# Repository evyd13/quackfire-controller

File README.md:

# Quackfire controller rev1

This is a replacement controller for the CM Quickfire Rapid. Everything works, except for the WinLock LED (which isn't connected to the controller).

## Building
If you feel like building a few of these PCBs yourself, go to the 'Releases' tab and download the latest gerber files. Order those at your favourite PCB manufacturer, get the components needed (see below) and solder them on! A hot air station is not required but a good soldering iron is. Flux is recommended.

## Opening the project
To open the files you will need the latest KiCAD nightly version.

## Bill of materials (BOM)
Amount is per PCB, multiply as needed.

| LCSC part # | Description             | Value | Package  | Amount |
| ----------- | ----------------------- | ----- | -------- | ------:|
| C83060      | Capacitor               | 0.1uF | 0603     | 4      |
| C131056     | Capacitor               | 4.7uF | 0805     | 1      |
| C302042     | Capacitor               | 1uF   | 0603     | 1      |
| C261942     | Fuse                    |       | 0805     | 1      |
| C98220      | Resistor                | 10K   | 0603     | 2      |
| C12028      | Resistor                | 5.1K  | 0603     | 2      |
| C384264     | Resistor                | 22    | 0603     | 2      |
| C44854      | MCU                     | 32U4  | QFP-44   | 1      |
| C341521     | Resonator               | 16MHz | SMD      | 1      |
|             | 2x10 2.00mm pin header  |       | THT      | 2      |

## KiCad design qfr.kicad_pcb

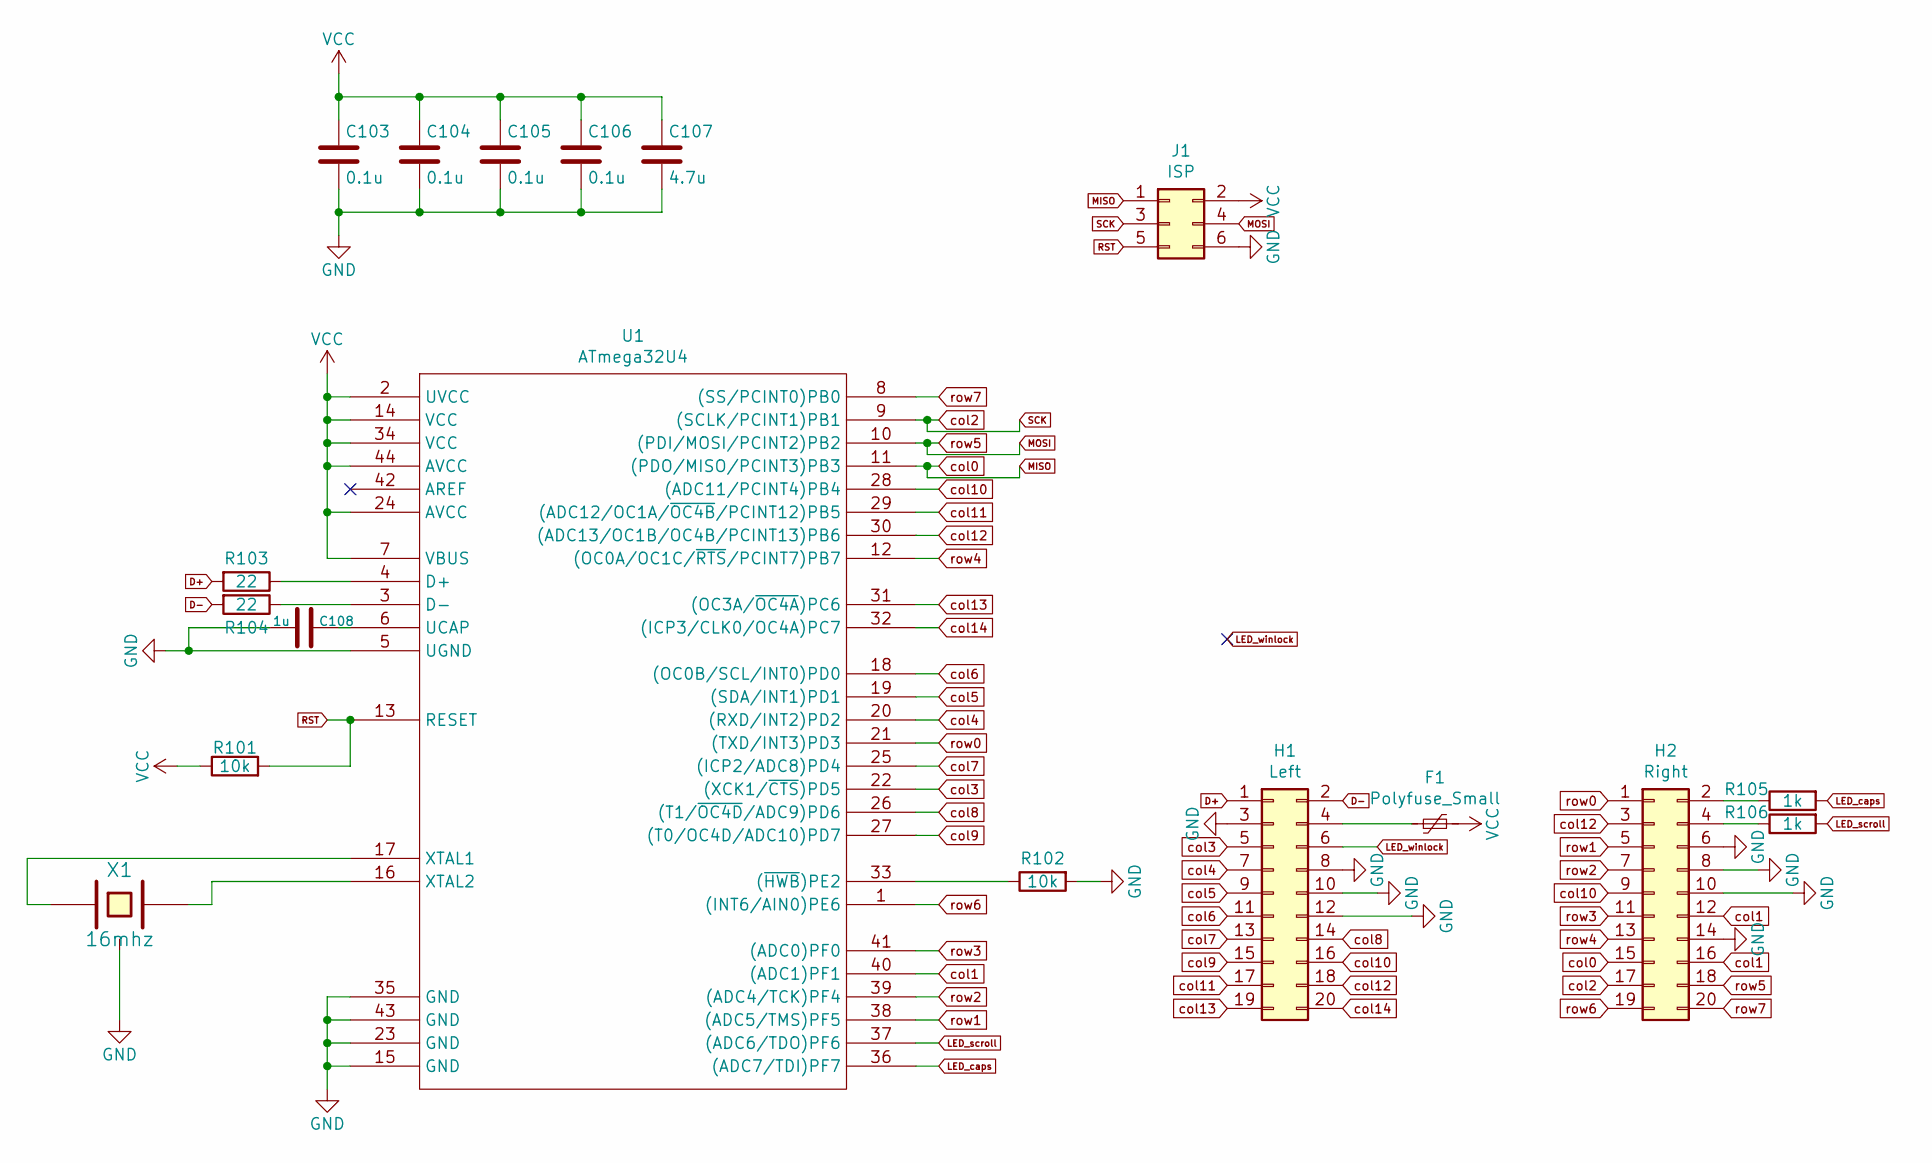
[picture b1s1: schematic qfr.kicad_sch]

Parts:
C103, C104, C105, C106: 0.1u; C_0603
C107: 4.7u; C_0805
C108: 1u; C_0603
F1: Polyfuse_Small; R_0805
H1: Left; PinHeader_2x10_P2.00mm_Vertical
H2: Right; PinHeader_2x10_P2.00mm_Vertical
J1: ISP; isp_standard
R101, R102: 10k; R_0603
R103, R104: 22; R_0603
R105, R106: 1k; R_0603
U1: ATmega32U4; ATMEGA32U4
X1: 16mhz; Resonator_SMD_muRata_CSTNExxV-3Pin-p1.2

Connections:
D+: H1.1, R103.2
D-: H1.2, R104.2
GND: C103.2, C104.2, C105.2, C106.2, C107.2, C108.2, H1.3, H1.8, H1.10, H1.12, H2.6, H2.8, H2.10, H2.14, J1.6, R102.2, U1.5 (UGND), U1.15 (GND), U1.23 (GND), U1.35 (GND), U1.43 (GND), X1.3
LED_caps: R105.2, U1.36 ((ADC7/TDI)PF7)
LED_scroll: R106.2, U1.37 ((ADC6/TDO)PF6)
MISO: H2.15, J1.1, U1.11 ((PDO/MISO/PCINT3)PB3)
MOSI: H2.18, J1.4, U1.10 ((PDI/MOSI/PCINT2)PB2)
unnamed: C108.1, U1.6 (UCAP)
unnamed: F1.1, H1.4
unnamed: H2.2, R105.1
unnamed: H2.4, R106.1
unnamed: R102.1, U1.33 ((~HWB~)PE2)
unnamed: R103.1, U1.4 (D+)
unnamed: R104.1, U1.3 (D-)
unnamed: U1.16 (XTAL2), X1.2
unnamed: U1.17 (XTAL1), X1.1
RST: J1.5, R101.2, U1.13 (RESET)
SCK: H2.17, J1.3, U1.9 ((SCLK/PCINT1)PB1)
VCC: C103.1, C104.1, C105.1, C106.1, C107.1, F1.2, J1.2, R101.1, U1.2 (UVCC), U1.7 (VBUS), U1.14 (VCC), U1.24 (AVCC), U1.34 (VCC), U1.44 (AVCC)
col1: H2.12, H2.16, U1.40 ((ADC1)PF1)
col3: H1.5, U1.22 ((XCK1/~CTS~)PD5)
col4: H1.7, U1.20 ((RXD/INT2)PD2)
col5: H1.9, U1.19 ((SDA/INT1)PD1)
col6: H1.11, U1.18 ((OC0B/SCL/INT0)PD0)
col7: H1.13, U1.25 ((ICP2/ADC8)PD4)
col8: H1.14, U1.26 ((T1/~OC4D~/ADC9)PD6)
col9: H1.15, U1.27 ((T0/OC4D/ADC10)PD7)
col10: H1.16, H2.9, U1.28 ((ADC11/PCINT4)PB4)
col11: H1.17, U1.29 ((ADC12/OC1A/~OC4B~/PCINT12)PB5)
col12: H1.18, H2.3, U1.30 ((ADC13/OC1B/OC4B/PCINT13)PB6)
col13: H1.19, U1.31 ((OC3A/~OC4A~)PC6)
col14: H1.20, U1.32 ((ICP3/CLK0/OC4A)PC7)
row0: H2.1, U1.21 ((TXD/INT3)PD3)
row1: H2.5, U1.38 ((ADC5/TMS)PF5)
row2: H2.7, U1.39 ((ADC4/TCK)PF4)
row3: H2.11, U1.41 ((ADC0)PF0)
row4: H2.13, U1.12 ((OC0A/OC1C/~RTS~/PCINT7)PB7)
row6: H2.19, U1.1 ((INT6/AIN0)PE6)
row7: H2.20, U1.8 ((SS/PCINT0)PB0)

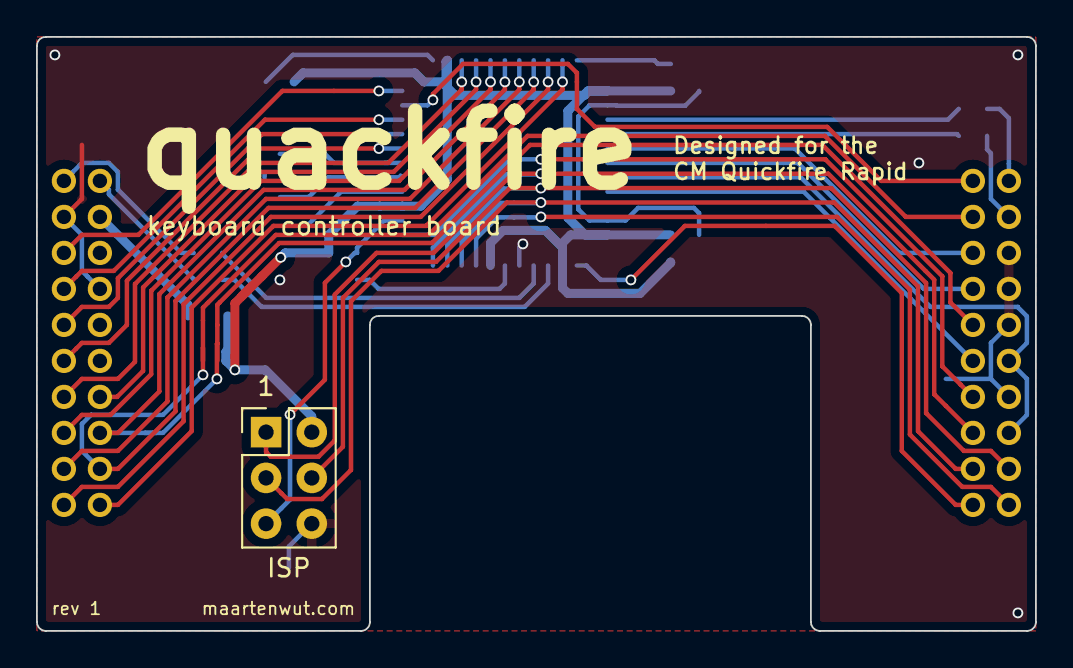
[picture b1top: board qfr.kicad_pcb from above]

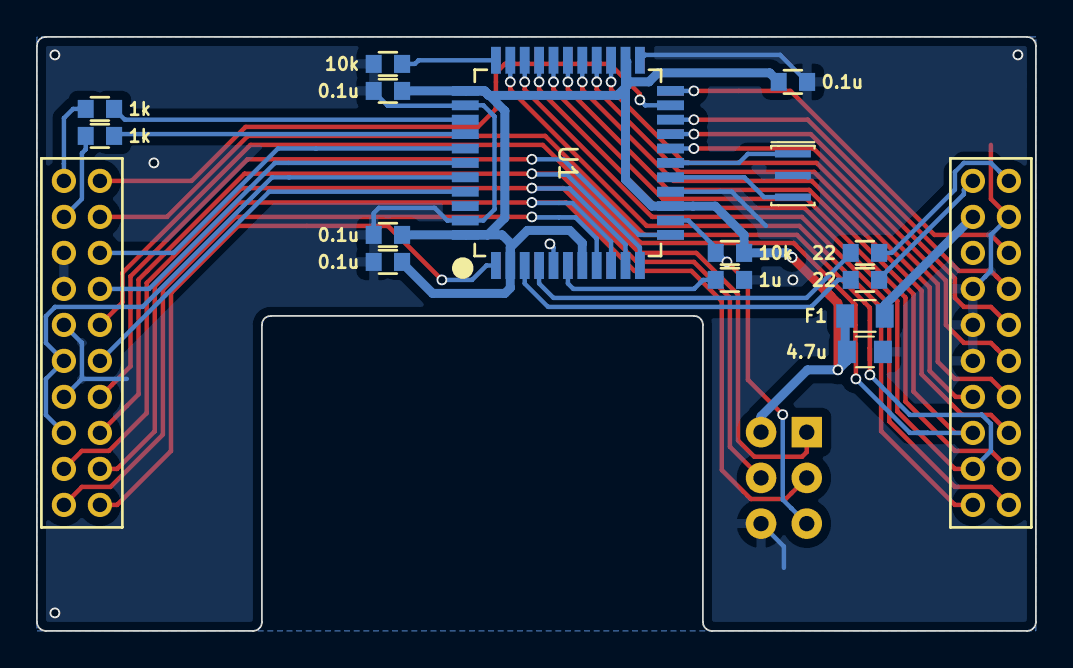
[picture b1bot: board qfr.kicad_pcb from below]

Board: 2 copper layers, 55.5 x 33.0 mm, 18 parts (15 on the bottom side), 39 nets.

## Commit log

2020-08-07 upload files
